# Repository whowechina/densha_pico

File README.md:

# Densha pico - Densha De Go! Style Controller
[点这里可以切换到中文版](README_CN.md)

It's XXXXX.

## Features
* XXX
* YYY

## Thanks
Thanks to many respectful guys/companies who made their tools or materials free or open source (KiCad, OnShape, InkScape, Raspberry things).

Special thanks to community projects and developers.
And also these projects:
* RP_Silicon_KiCad: https://github.com/HeadBoffin/RP_Silicon_KiCad

## My Other Projects
You can check out my other cool projects.

* Popn Pico: https://github.com/whowechina/popn_pico
* IIDX Pico: https://github.com/whowechina/iidx_pico
* Chu Pico: https://github.com/whowechina/chu_pico
* Mai Pico: https://github.com/whowechina/mai_pico
* Diva Pico: https://github.com/whowechina/diva_pico
* AIC Pico: https://github.com/whowechina/aic_pico
* Groove Pico: https://github.com/whowechina/groove_pico
* Geki Pico: https://github.com/whowechina/geki_pico
* Musec Pico: https://github.com/whowechina/musec_pico
* Ju Pico: https://github.com/whowechina/ju_pico
* Bishi Pico: https://github.com/whowechina/bishi_pico
* Nos Pico: https://github.com/whowechina/nos_pico
* Voltex Pico: https://github.com/whowechina/voltex_pico
* Chord Pico: https://github.com/whowechina/chord_pico
* Dance Pico: https://github.com/whowechina/dance_pico
* Densha pico: https://github.com/whowechina/densha_pico

## **Disclaimer** ##
I made this project in my personal time with no financial benefit or sponsorship. I will continue to improve the project. I have done my best to ensure that everything is accurate and functional, there's always a chance that mistakes may occur. I cannot be held responsible for any loss of your time or money that may result from using this open source project. Thank you for your understanding.

## About the License
It's CC-NC. So DIY for yourself and for your friend, don't make money from it. And plagiarism that doesn’t even dare to mention the original author is not acceptable. Please note that pooling orders and group buying for raw materials is acceptable.Selling any leftover components at cost (without profit) is also acceptable.

If you're interested in buying from me, or for commercial use, please contact me (Discord, QQ group, Goofish).
* My Discord Invitation: https://discord.gg/M8f2PPQFEA
* QQ Group: 854535476
* Goofish: whowe12345

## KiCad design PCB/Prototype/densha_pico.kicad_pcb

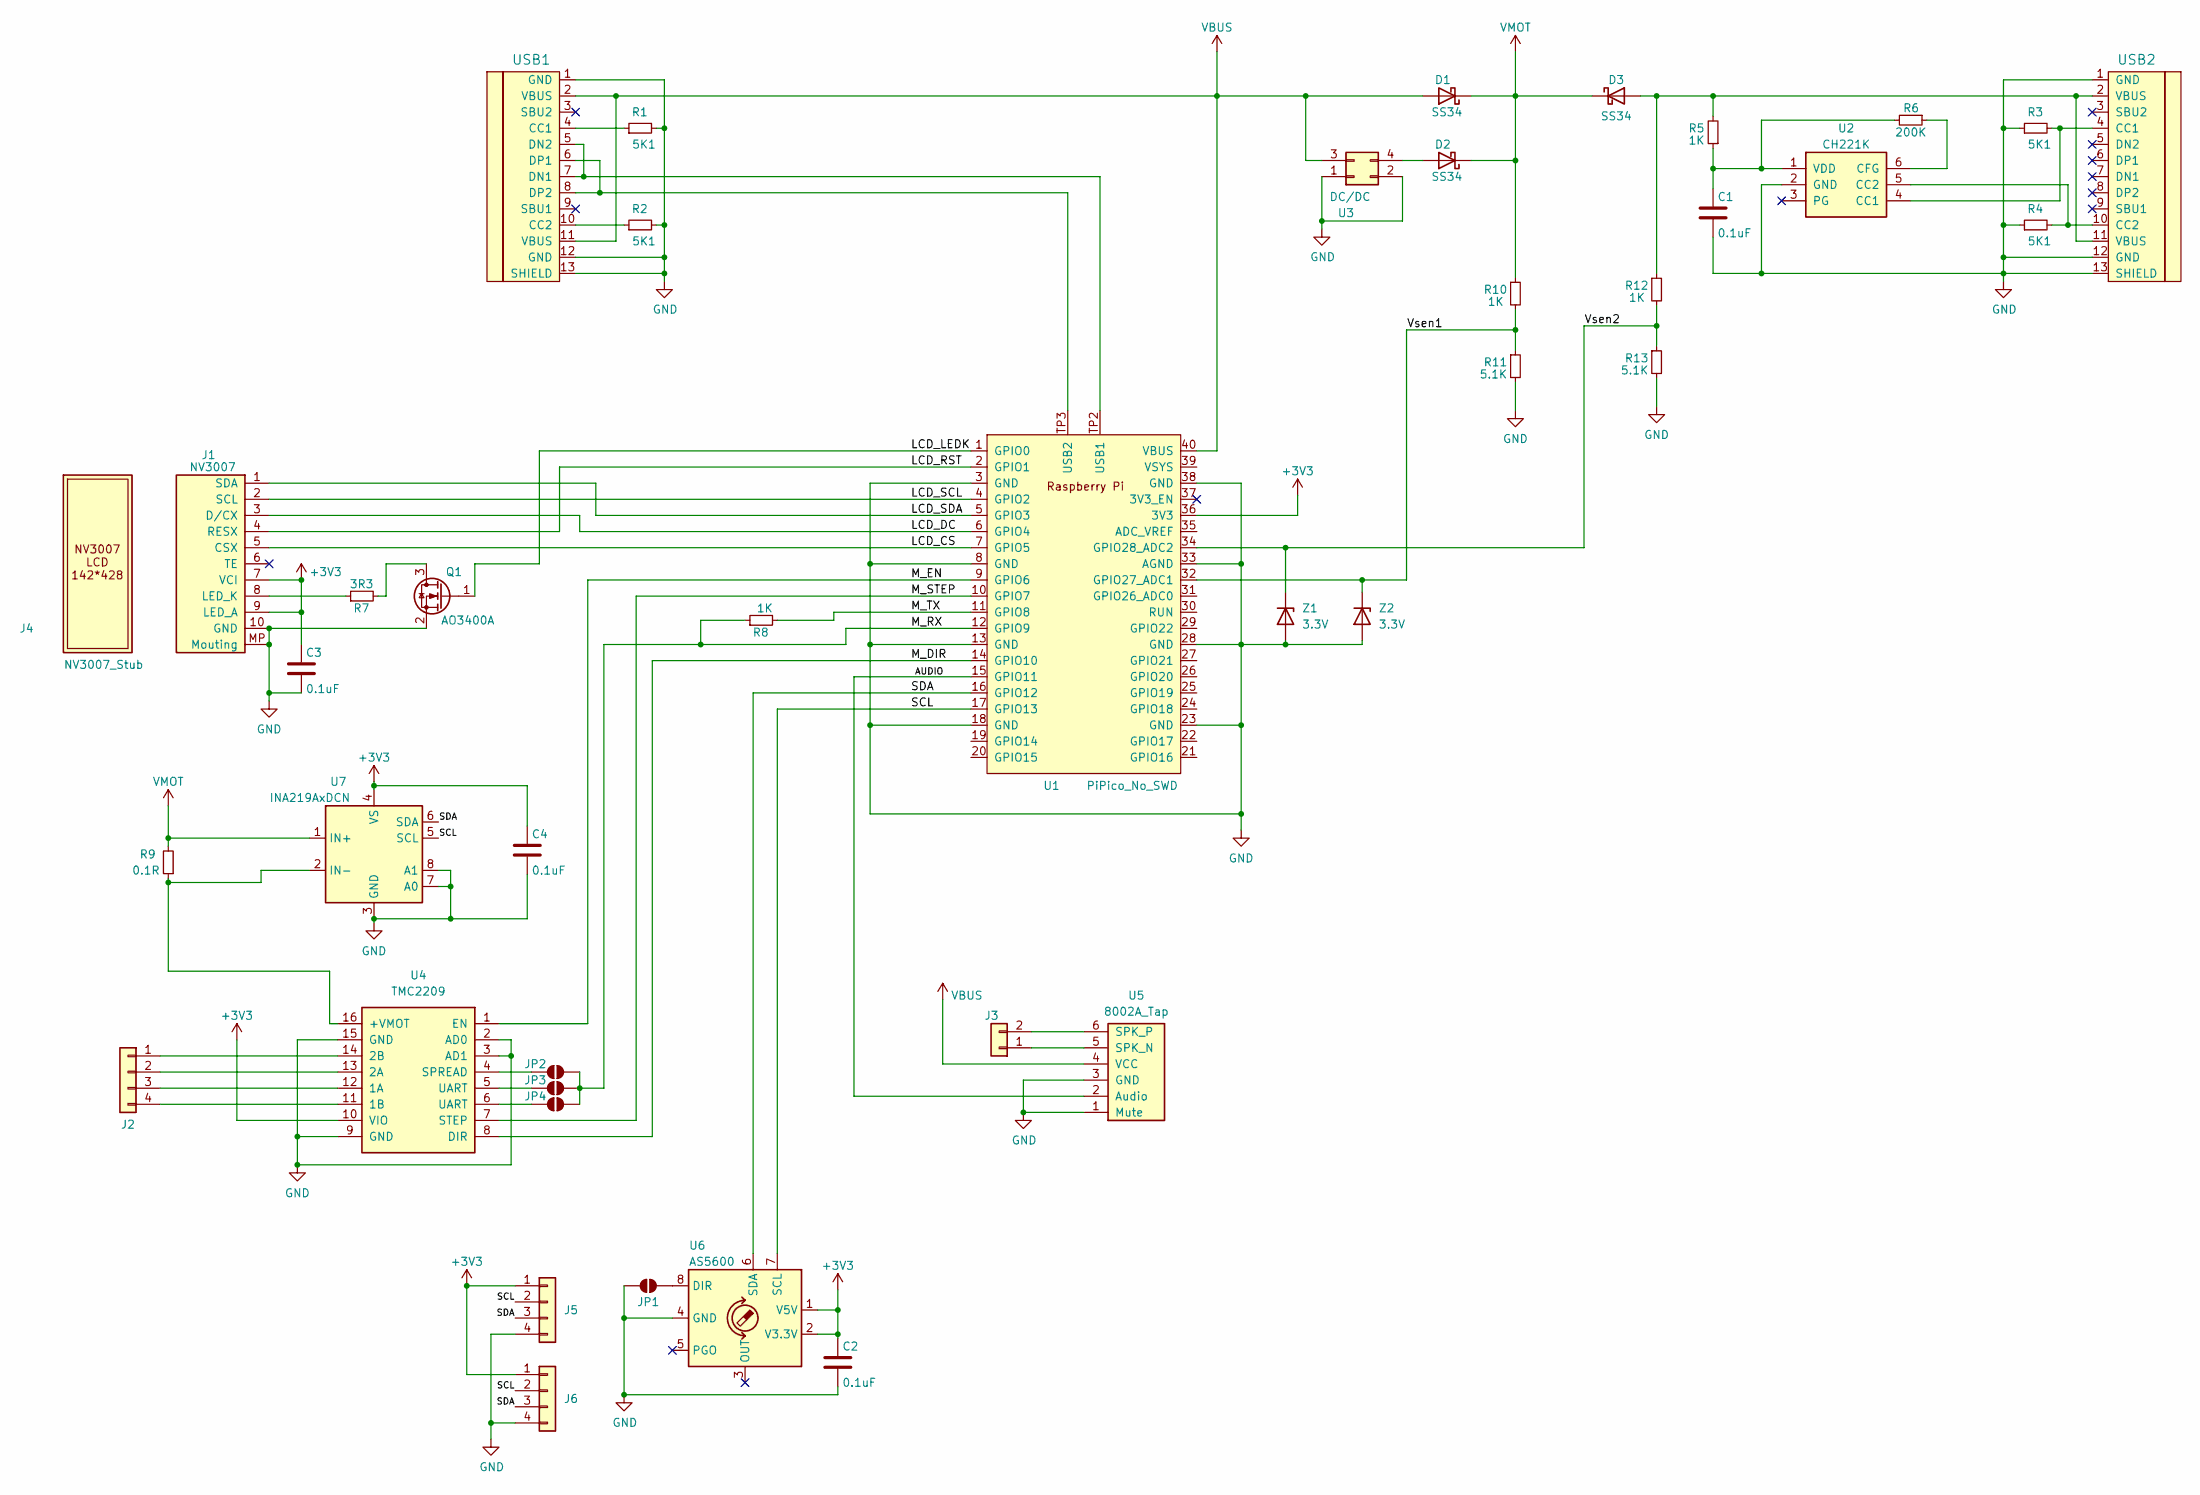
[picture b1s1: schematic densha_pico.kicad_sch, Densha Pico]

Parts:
C1, C2, C3, C4: 0.1uF; C_0603_1608Metric_Pad1.08x0.95mm_HandSolder
D1, D2, D3: SS34; D_SMA
J1: NV3007; FPC0.5_10P
J2: Conn_01x04; JST_EH_S4B-EH_1x04_P2.50mm_Horizontal
J3: Conn_01x02; Solder_2P
J4: NV3007_Stub
J5, J6: Spin; SH1.0_4P_Solder_Combo
JP1, JP2, JP3, JP4: DIR; SmallJumper
Q1: AO3400A; SOT-23
R1, R2, R3, R4: 5K1; R_0603_1608Metric_Pad0.98x0.95mm_HandSolder; LCSC C23186
R5, R8, R10, R12: 1K; R_0603_1608Metric_Pad0.98x0.95mm_HandSolder; LCSC C23186
R6: 200K; R_0603_1608Metric_Pad0.98x0.95mm_HandSolder; LCSC C23186
R7: 3R3; R_0603_1608Metric_Pad0.98x0.95mm_HandSolder; LCSC C23186
R9: 0.1R; L_1206_3216Metric_Pad1.42x1.75mm_HandSolder; LCSC C23186
R11, R13: 5.1K; R_0603_1608Metric_Pad0.98x0.95mm_HandSolder; LCSC C23186
U1: PiPico_No_SWD; RPi_Pico_SMD_Pins_No_SWD
U2: CH221K; TSOT-23-6_HandSoldering
U3: DC/DC; DCDC_3to5
U4: TMC2209; TMC2209_16P
U5: 8002A_Tap; 8002A_TAP
U6: AS5600; SOIC-8_3.9x4.9mm_P1.27mm
U7: INA219AxDCN; SOT-23-8_Thin
USB1: Data; HRO-TYPE-C-31-M-12-Assembly
USB2: PD; HRO-TYPE-C-31-M-12-Assembly
Z1, Z2: 3.3V; D_SOD-123F

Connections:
+3V3: C2.1, C3.1, C4.1, J1.7 (VCI), J1.9 (LED_A), J5.1, J6.1, U1.36 (3V3), U4.10 (VIO), U6.1 (V5V), U6.2 (V3.3V), U7.4 (VS)
/AUDIO: U1.15 (GPIO11), U5.2 (Audio)
/LCD_CS: J1.5 (CSX), U1.7 (GPIO5)
/LCD_DC: J1.3 (D/CX), U1.6 (GPIO4)
/LCD_LEDK: Q1.1 (G), U1.1 (GPIO0)
/LCD_RST: J1.4 (RESX), U1.2 (GPIO1)
/LCD_SCL: J1.2 (SCL), U1.4 (GPIO2)
/LCD_SDA: J1.1 (SDA), U1.5 (GPIO3)
/M_DIR: U1.14 (GPIO10), U4.8 (DIR)
/M_EN: U1.9 (GPIO6), U4.1 (EN)
/M_RX: JP2.2 (B), JP3.2 (B), JP4.2 (B), R8.1, U1.12 (GPIO9)
/M_STEP: U1.10 (GPIO7), U4.7 (STEP)
/M_TX: R8.2, U1.11 (GPIO8)
/SCL: J5.2, J6.2, U1.17 (GPIO13), U6.7 (SCL), U7.5 (SCL)
/SDA: J5.3, J6.3, U1.16 (GPIO12), U6.6 (SDA), U7.6 (SDA)
/Vsen1: R10.2, R11.1, U1.32 (GPIO27_ADC1), Z2.1 (K)
/Vsen2: R12.2, R13.1, U1.34 (GPIO28_ADC2), Z1.1 (K)
GND: C1.2, C2.2, C3.2, C4.2, J1.10 (GND), J1.MP (Mouting), J5.4, J6.4, JP1.1 (A), Q1.2 (S), R1.2, R2.2, R3.1, R4.1, R11.2, R13.2, U1.3 (GND), U1.8 (GND), U1.13 (GND), U1.18 (GND), U1.23 (GND), U1.28 (GND), U1.33 (AGND), U1.38 (GND), U2.2 (GND), U3.1, U3.2, U4.2 (AD0), U4.3 (AD1), U4.9 (GND), U4.15 (GND), U5.1 (Mute), U5.3 (GND), U6.4 (GND), U7.3 (GND), U7.7 (A0), U7.8 (A1), USB1.1 (GND), USB1.12 (GND), USB1.13 (SHIELD), USB2.1 (GND), USB2.12 (GND), USB2.13 (SHIELD), Z1.2 (A), Z2.2 (A)
unnamed: D2.2 (A), U3.4
unnamed: D3.2 (A), R5.2, R12.1, USB2.2 (VBUS), USB2.11 (VBUS)
unnamed: J1.8 (LED_K), R7.1
unnamed: J2.1, U4.14 (2B)
unnamed: J2.2, U4.13 (2A)
unnamed: J2.3, U4.12 (1A)
unnamed: J2.4, U4.11 (1B)
unnamed: J3.1, U5.5 (SPK_N)
unnamed: J3.2, U5.6 (SPK_P)
unnamed: JP1.2 (B), U6.8 (DIR)
unnamed: JP2.1 (A), U4.4 (SPREAD)
unnamed: JP3.1 (A), U4.5 (UART)
unnamed: JP4.1 (A), U4.6 (UART)
unnamed: Q1.3 (D), R7.2
unnamed: U1.TP2 (USB1), USB1.5 (DN2), USB1.7 (DN1)
unnamed: U1.TP3 (USB2), USB1.6 (DP1), USB1.8 (DP2)
unnamed: R3.2, U2.4 (CC1), USB2.4 (CC1)
unnamed: R4.2, U2.5 (CC2), USB2.10 (CC2)
unnamed: R6.1, U2.6 (CFG)
unnamed: C1.1, R5.1, R6.2, U2.1 (VDD)
unnamed: R9.1, U4.16 (+VMOT), U7.2 (IN-)
unnamed: R1.1, USB1.4 (CC1)
unnamed: R2.1, USB1.10 (CC2)
VBUS: D1.2 (A), U1.40 (VBUS), U3.3, U5.4 (VCC), USB1.2 (VBUS), USB1.11 (VBUS)
VMOT: D1.1 (K), D2.1 (K), D3.1 (K), R9.2, R10.1, U7.1 (IN+)

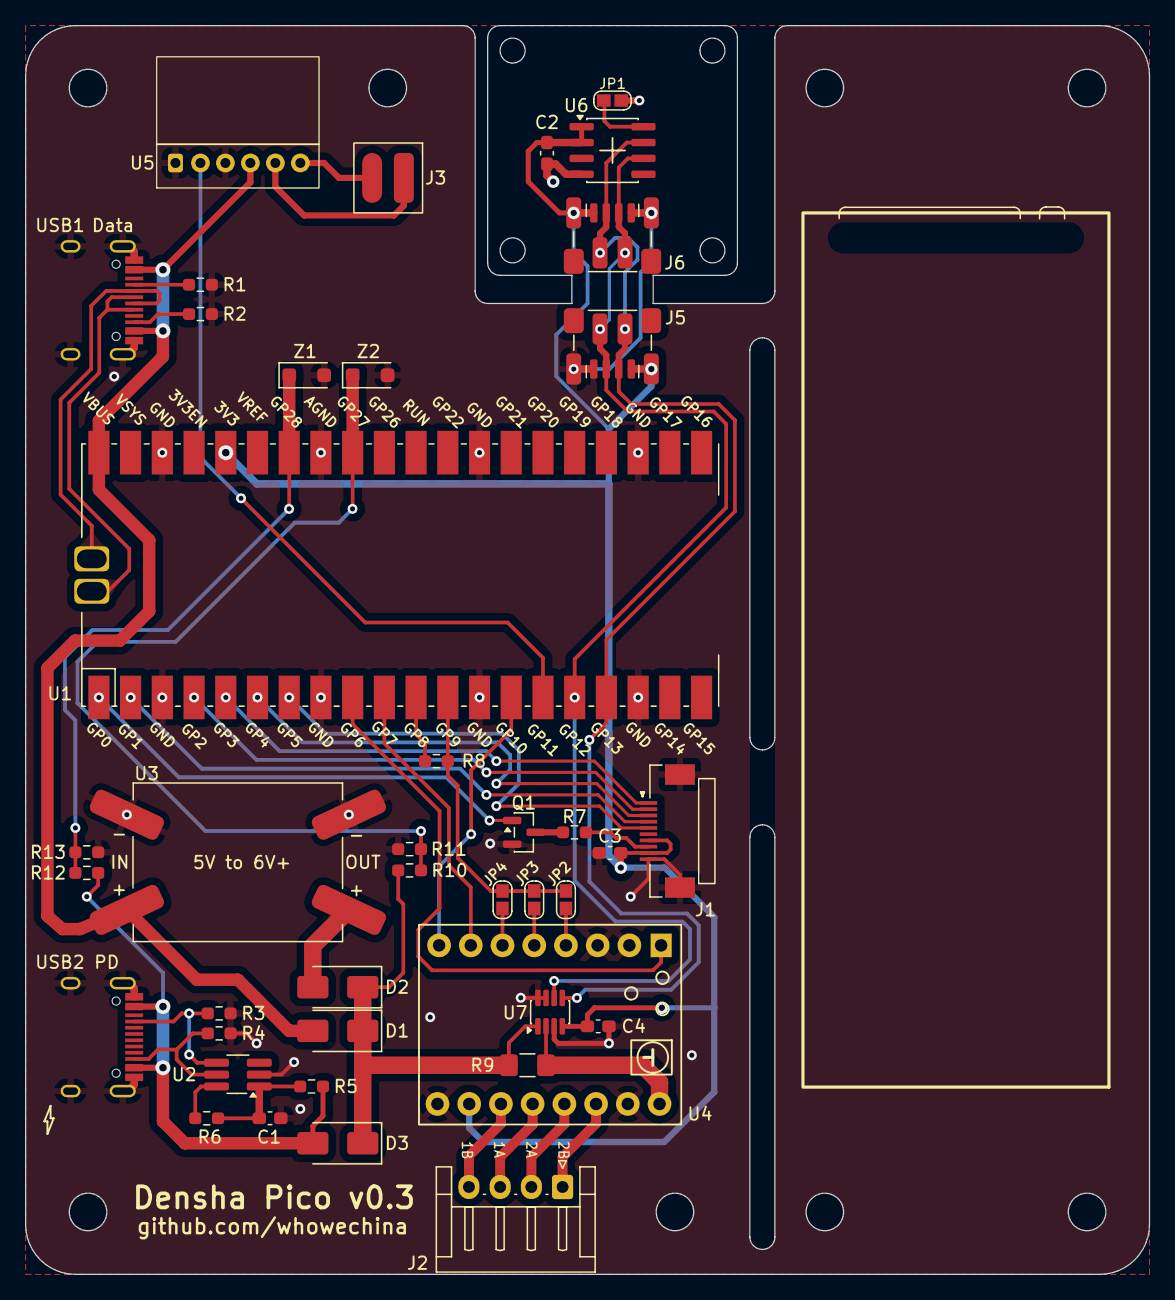
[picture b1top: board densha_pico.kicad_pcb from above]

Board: 2 copper layers, 90.0 x 100.0 mm, 42 parts (0 on the bottom side), 43 nets.

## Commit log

2026-03-24 Initial commit, nv3007 works
2026-03-25 Prototype PCB progress 40%
2026-03-30 Firmware works on PCB with Pico 2
2026-03-30 PCB v0.2
2026-03-31 Remove soft crop
2026-03-31 Safer savedata location
2026-03-31 Replace io lock with official block
2026-03-31 Remove st7789 files
2026-03-31 PCB v0.3
2026-04-01 Finalize official block mechanism
2026-04-02 Official flash safe operation
2026-04-02 Mascon current set and debug
